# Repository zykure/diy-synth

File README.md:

# diy-synth

Schematics and related files for DIY modular synthesizer components.

## MS-20 VCF

[A voltage controller filter based on the Korg MS-20 design.](./VCF_MS-20)

## AS3340 VCO

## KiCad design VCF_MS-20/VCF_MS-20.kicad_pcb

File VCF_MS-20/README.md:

# diy-synth

Schematics and related files for DIY modular synthesizer components.

## MS-20 VCF

A voltage controlled filter based on the "late" Korg MS-20 design. Original design schematics from [Rene Schmitz](https://www.schmitzbits.de/ms20.html) and [Eddy Bergman](https://www.eddybergman.com/2019/12/synthesizer-build-part-12-korg-ms20.html?m=1).

**Working Falstad circuit simulation (online):** [click here][1]

### Features

* Designed for Eurorack format with a 6 HP frontplate and standard +/- 12 V power supply.
* Frontplate potentiometers to control filter cutoff, resonance, input level, and cutoff CV amount.
* Input jacks for source audio signal and cutoff CV; output jack for filtered audio signal.
* Quad opamp (LM324N) and dual OTA (LM13700) in the main circuit.
* LEDs in the resonance feedback circuit indicate resonance "drive".

### Layout

* Circuit schematics: [VCF_MS-20_plan.pdf](./schematics/VCF_MS-20_plan.pdf)
* Board layout: [VCF_MS-20_pcb.pdf](./schematics/VCF_MS-20_pcb.pdf) ([*mirrored*](./schematics/VCF_MS-20_pcb_mir.pdf))
   * The board is a 21 x 36 hole (56 x 97 mm) perforated PCB that should fit in most Eurorack cases. The required depth is about 60 mm.
* Board layout with frontplate design: [VCF_MS-20_pcb_all.pdf](./schematics/VCF_MS-20_pcb_all.pdf)
   * The frontplate is designed for Eurorack cases and has a size of 3 U x 6 HP (127 x 30.5 mm)

### Components (BOM)

*Estimated costs ~ 25 Euro* (in Germany, as of Nov 2023)

|Item |Qty  |Reference(s)                  |Value          |Datasheet                                         |Note           |
|----:|----:|-----------------------------:|--------------:|--------------------------------------------------|---------------|
|    1|    1|                            C1|           4.7n|~                                                 |               |
|    2|    2|                        C2, C3|           1.0n|~                                                 |film cap.      |
|    3|    2|                        C4, C5|           100n|~                                                 |               |
|    4|    1|                            C6|           1.0u|~                                                 |optional       |
|    5|    1|                            C8|           470n|~                                                 |film cap.      |
|    6|    2|                        D1, D2|            LED|~                                                 |               |
|    7|    1|                            J1|          POWER|~                                                 |               |
|    8|    1|                            J2|       AUDIO IN|~                                                 |               |
|    9|    1|                            J3|      AUDIO OUT|~                                                 |               |
|   10|    1|                            J4|          CV IN|~                                                 |               |
|   11|    2|                        Q1, Q2|         BC558C|https://www.onsemi.com/pub/Collateral/BC556BTA-D.pdf|matched      |
|   12|    1|                            R1|           200k|~                                                 |optional       |
|   13|    2|                        R2, R3|           100k|~                                                 |               |
|   14|    6|       R4, R5, R6, R7, R9, R10|            10k|~                                                 |               |
|   15|    1|                            R8|           8.2k|~                                                 |or trimpot     |
|   16|    1|                           R11|           4.7k|~                                                 |               |
|   17|    1|                           R12|           470k|~                                                 |               |
|   18|    1|                           R13|           2.2k|~                                                 |               |
|   19|    1|                           R14|           1.5k|~                                                 |               |
|   20|    4|            R15, R16, R17, R18|            220|~                                                 |               |
|   21|    2|                      RV1, RV4|    100k / log.|~                                                 |Resonance/Input level ctrl.|
|   22|    2|                      RV2, RV3|    100k / lin.|~                                                 |Cutoff/CV amount ctrl.|
|   23|    1|                           SW1|     SW_DPDT_x2|~                                                 |HP/LP mode     |
|   24|    1|                           SW2|        SW_SPDT|~                                                 |6/12 dB falloff|
|   25|    1|                            U1|          LM324|http://www.ti.com/lit/ds/symlink/lm2902-n.pdf     |               |
|   26|    1|                            U2|        LM13700|http://www.ti.com/lit/ds/symlink/lm13700.pdf      |               |

Notes:
* Use film capacitors in the audio signal path, not ceramic ones. (Ceramic ones have a voltage dependency that causes distortions.)
* The feedback resistor R8 may be tuned to change the resonance characteristics, e.g. a trimpot could be used instead of a fixed resistor. Check out the [circuit simulation][1] to see what this does.
* For best results, the two transistors should be matched by their hFE value as good as possible. This can usually be done with a simple multimeter with transistor tester.
* A passive low-pass filter (R1/C6) is added at the audio input to remove any DC voltage offset. This is completely optional and the components could be removed from the circuit.

[1]: https://falstad.com/circuit/circuitjs.html?ctz=CQAgbArCAMB00OgRgCwE4Oa9kAme0AHBBAMxhq6lKEDsYt4uISzGMBiSAUCtMyiRg8fEBFYjoLGAB0AztHl95AWlbzFCjbCibNyueq3G4u+UlVI49amFK1SpCLRpG4KUkRpokaMNAg0IipzBHkAEwBTADMAQwBXABsAF1lDVXdPQm9ff0Dg0m0PALAUXH8qXGgnFFDNKLik1M0LE1hiiFLy-lIqmrqImISUtNa1JHg0QQh0NFJCXFxOiCLcFzpqANol3pQVwzC5BuHm80sJ3BRaaG3CDbBSpEKFWHswXFY7h4+iHwGjoZNNJqVbrbp0Si+ba0DLtcqUbIOPi4KZ-A71QEjTQg4wqdzw3CI0jI1GtKwYxpYyzyRawFFIWh0D7XB7IMCwspg-wQj5oaH-Y5A7GtOBvH4oQh8hYQQgoSCw+yBToLQlVJDOZ7kwaU05yHHY0W0JVgFULZAagWY3U4wiwWUea78YhlB5jQ3vKwSqVLWXy9Hak6jDSrChUa60dA3NAQXCWnVBvX4lyMlG7QjQFCCEOUew3SO0aOx-0A+MtSykHTocjQSDZdVGwighkLOaXdOZsmHQVU9K4uDVMoS3zUQQ3ba1Yvd3Ui7Rs7bvLJWchgdVxk7cWLgFCSFgSS5SQgsZhqZjkxBSftOWwFwJOD6eZiXsgM1A+aoMqiHs8IDcgOXb8YBCEEBAJANAjxAiRvwQED+3PGVxGoZkyiQGgZl0Fhz2gbgAHcjy-Sg-wIx9cPwndUOYfcYFIiUWEI2jFm3bC8IYy4tzwNjmLEQjGLEegOKY0jnGEXjhLoki8LE3xmEgYRpOovDZJ3UopCorjxEo0QxLUoT+Ko7TOgUviRMMwJKMMriGNEBiLJow8lmEUo8FsvDeikQRhFojyjJszzD08QTJL00z+IC6iAGMiJAMLaMcYQpCQSIVHAlR8BNXlCDvGsqEIuCeEisSwsK8gYBYJLwPwPhiXeWtnUCBwOAQHgWP8kqvOA7CACcWEzcieNEBLzxomCqkPbzRqM+ZtyEdzgJmoylPkxb-AWwz5v-FgVq6v85pWjb5sGxBuG60D5pUJyDswo68NOla1F6g7SPO6aVs+TaL1It6GTkwlxOo7qprwO5otlaKStUqpjrBkTgbi6HSsWLjAcJfzQbWCT4fRzHge2+7txRyDerhiHcfkgm1EI4mONxhyd1Sogd0On8TvIfyYxA1m-xg1SsO4SKVD4KQwoF3poozUq4K4DhMwwbKHnEdsXEa5Ans5u8OZNMXBO67yPAEJy9YRqpLJgw3ddF7ChGYOGNK5qRbeYKcVESSJwmkC9Gp4K27bEImSpmfGQCdl23aQCXPdIm2JDcsQJCR-2iaqX3AuipOA9T+24+G9zRcBw2Tft3rBdjkiAba9MQe3CUPbNJHQern2G-jvyhaTpvuAZbc7hz5hu+izWw+gjgFgYLCx7DgAlSI5AAewAO1iOfwsiJ7DeFhuwuw1JUAAivvpAiupDUWD4HEOYHHQp4Fkyw88R0BAKDIfgM3QI0w4gGCp24VJyYr2mVEPpBXcsBWCoGyBQBwDYygn0zHQGM0A-AfElNsKAH8pBfxuqLQBh8aJ+DwAzdAwgcEsTwRXDaOCdbATIU5QB34oYHncoeWhQ08L-ycv-Dqn1+LJTktwiiRl96gQ4VnVhhkhFiLwVxYR1sSqgW2nDUCgM5F-kdHzH2PD1FOXcrAR0Y8sKJWShwBCTwWQbEcPVZWzV1F4OLnI7OIEDYwQFoeAuIFaKCNolxDxX5uFaJok5DRDcNGWQroE0Jni7JHy8k4iJ3VBGi33h1FRLCWDcPcdwi2n1eoAIShIHJRk1AiWsvZAapElJUWuPjUpN1i7CzVuLEJIA-6GWITtIhqkWkfWRJBPcohCnkTSPoYURY9DaDMMYAwbhgwvHGWMKwOi3iEEgFMRkxByhFEXJKKEVwaylE1F2K0CY77FGyFsvkOyHgeA2SUMogQMBUBUvsikgYyxtA6F0O5OZHlriFGcPUqEQF+FYMUQkQgVwwheHwIQko1jvD4IQiFWoSwvL+eMEBJIyAFlbOmZ4+J+AYGfGfdU6zJyHOFEUNkayoyMmjMgZ4xzkAeFQFNJwfI-A-J7PqDkjKRwsvquy0lpZqRyFpKQc+DgUTlCeP+bl0L4EFhpR-J4HLrQijhPi9AgsEFzFQByY2VUIzIHNHYRFByhX-Omcc-V1RDVWHVCalVwIyQTGBcSI0rN6ARj1RqqYiAMAjkda8vQ7RGVrDuPaGsGZ2SCpRb2Bl0LmQ7HJCMkNqAw13EzJGuUgbUUAsqFUa4dwnj2v2O4SlibnwICLEiqcCZg0IHTMgFE58+AXz9DWslfyDTwCsNyaM+Q9gLEcBODtOpVaUQZioLBH1XKg1ArY-hllgLzqcYu-xAE3pBLettfhU7TxQXiiwNBn08kJLyRQtxt9AH5KZj+TukFfqgRPLfdxV1EAcF6DQPRWFSAgAAMLxGSDPaI0Qnq7vCVemdpV8ngY+gAcw1mNJxnNvLwcgpTWR8l1ZobxvDXD2HqIIbhsRkqBHsJEdBsRyj7M0MxlasIW2VNyN-gNqLBu+dCNESPpuvBz6JbcAQ-wua0dHzUQng+l9t83r9I9qIOOEsdDcHE3xp90md7hz6fJi8inlN0bw50IW4M-xi0GuHUwHdrggQdtsKzK0sZh0RtFeBmEWDcAAMqXqFuLFQjGGmlTiIkOQkQEZPWs8eB2ONQu-QUYx8GoXo6yMY0nbCnNnFeYAhvAepUACSc9uCczelRQrNmw4JTkMkeQAB5QD+XNblNEOUkrCM57hCqzVgr57cnHi+qVAAQgAS1iHIfLlmOEmWEAk-jm487ATht5cCeSoJjxYHSK4TxOh8hNAWdUK3LguHeEyWUkqGBvp-K5Nus22qcIQ33Q2t3PFidSXJXhfkNPcdE9piAAmgaQa1gfD22FKtNL-gzPwPMvwCN+kV3qOkbr8ImhTCdLiwP9W4zxSLcOYfA1w1jLiOObNCJs3j9TWMcfVPQ5pI+E1YeEyqdxh6W1Pq-XkoV8nxcJpwwmlIwyVFOfk754ZkSRPI4lV56Lhmdd8Y2fGsLxSPOGtrVypHUG81kay+chN8y7TqKbjMspUQVEvzddPMtyqA55hwrlJlGMUAzfVXKDKOqfJf3QVVprOp4tN61bGmNYCXlX1SAAGKRFdgAI1iOFAA1rwaopUG78PTglDwAB9QgyfoDJ48DMZPVgc-4DT2oZPuAc8p9IDH39Md+lr1E6hWgqf0+Z6vDnjPksEH0E6EsZPhfi+1+T2Xj4Yc+5UU24zaQM0YJWKHwzIf5OZ8HgrpzLiSyq4wT18XFLms1+r-ogHkAU9Z4LyXivSS9EYJ525uXsQv0G4qWTqVdUGe08Z6zygZPEB08gK70gIvOeP59+97Tu9IAT1mVhVnILlgAYDKrirszs1q1uAXlnhJlEjsDuDj5KbGxqbK0sXOxqviIhnFxgQahpHG3AvmnFnFVEwNuGFA4BNprLku-k-o3tnrnqwHaF-j-qhO-mXpQalMDLxokltEeqQPXs-jUB-vap3nAAXt-j3mQP-rwXpt5ALFgR7KhCIUwS-s3hIRwT3k8AobHngmFLxIvruK-poeIbnnAN-t3jnqgAYb+rxEYezJdOqOYQ3lodYR3u-tYbob-q-jwbHpKD9F+PwNNLlEeBoR4ZYS3p-oXvlCAIyPjNPqLFzn+Dot+mPBAElIwNIVMJlFbs7iavYJYqRLQfgoeEkRUUZJUk9okeLPJFxLURUuLLxE0Q0XpMDPvF4szvxF9IzgAB6JE7ZoSJEPTAzTTbjRrhC9akQEyJK9HxRzHy4JSo7UQeblETTNES7+axCBbBaqTcBDEuD4zzCJHiAiBhyTFHgRCzGSTRaaypQ2aL7uZiArTqx6YEZhwBZBYhZBQTb+yhQ0a6QTbswGZOYkQeZTqe7eZYyby7H7F-EgRwlJxPHWz0FPRYzkxYnk5ol0y0w6RDHQkV4lF8FQDEjuQ9QgAAASAACkcRzCNJlMicyYSJ5FSQADL0lDFkAAn2xkBgy-rXFckMkzBCzZBiAyiVzGaoA0n0lw48STpkylKUH7zglhTchx6MHRHyH4A+EECSHv62F7AOF1GEJ-aJ5-juFiG6k6Af4IBIRGmyGZ4BGX77xrzixNyxyiHMEiF6n2lNTRiOl+HiD-4zy7gu6Horh7DTTaZSyqQRnRTcDhnqFNKlQsivQVhWBE6cCDx4CJll4plUCbT370BppiAGnNqfqKjoAuK5n5k8BFm-ouL1GshiAcBhwu75aHgXGB6lb37nhALB5h4R6R7yD779blaLzLzdmYSMB9nRQIxoJAJuYzzxCdTLzyCB6dSRAACO8QkQS8AAnrOWCiAAuQlJwJkVwDkRWdeeeAYowMfNVskAAA6AbyB-qxCvkR79bJDTkrxAA

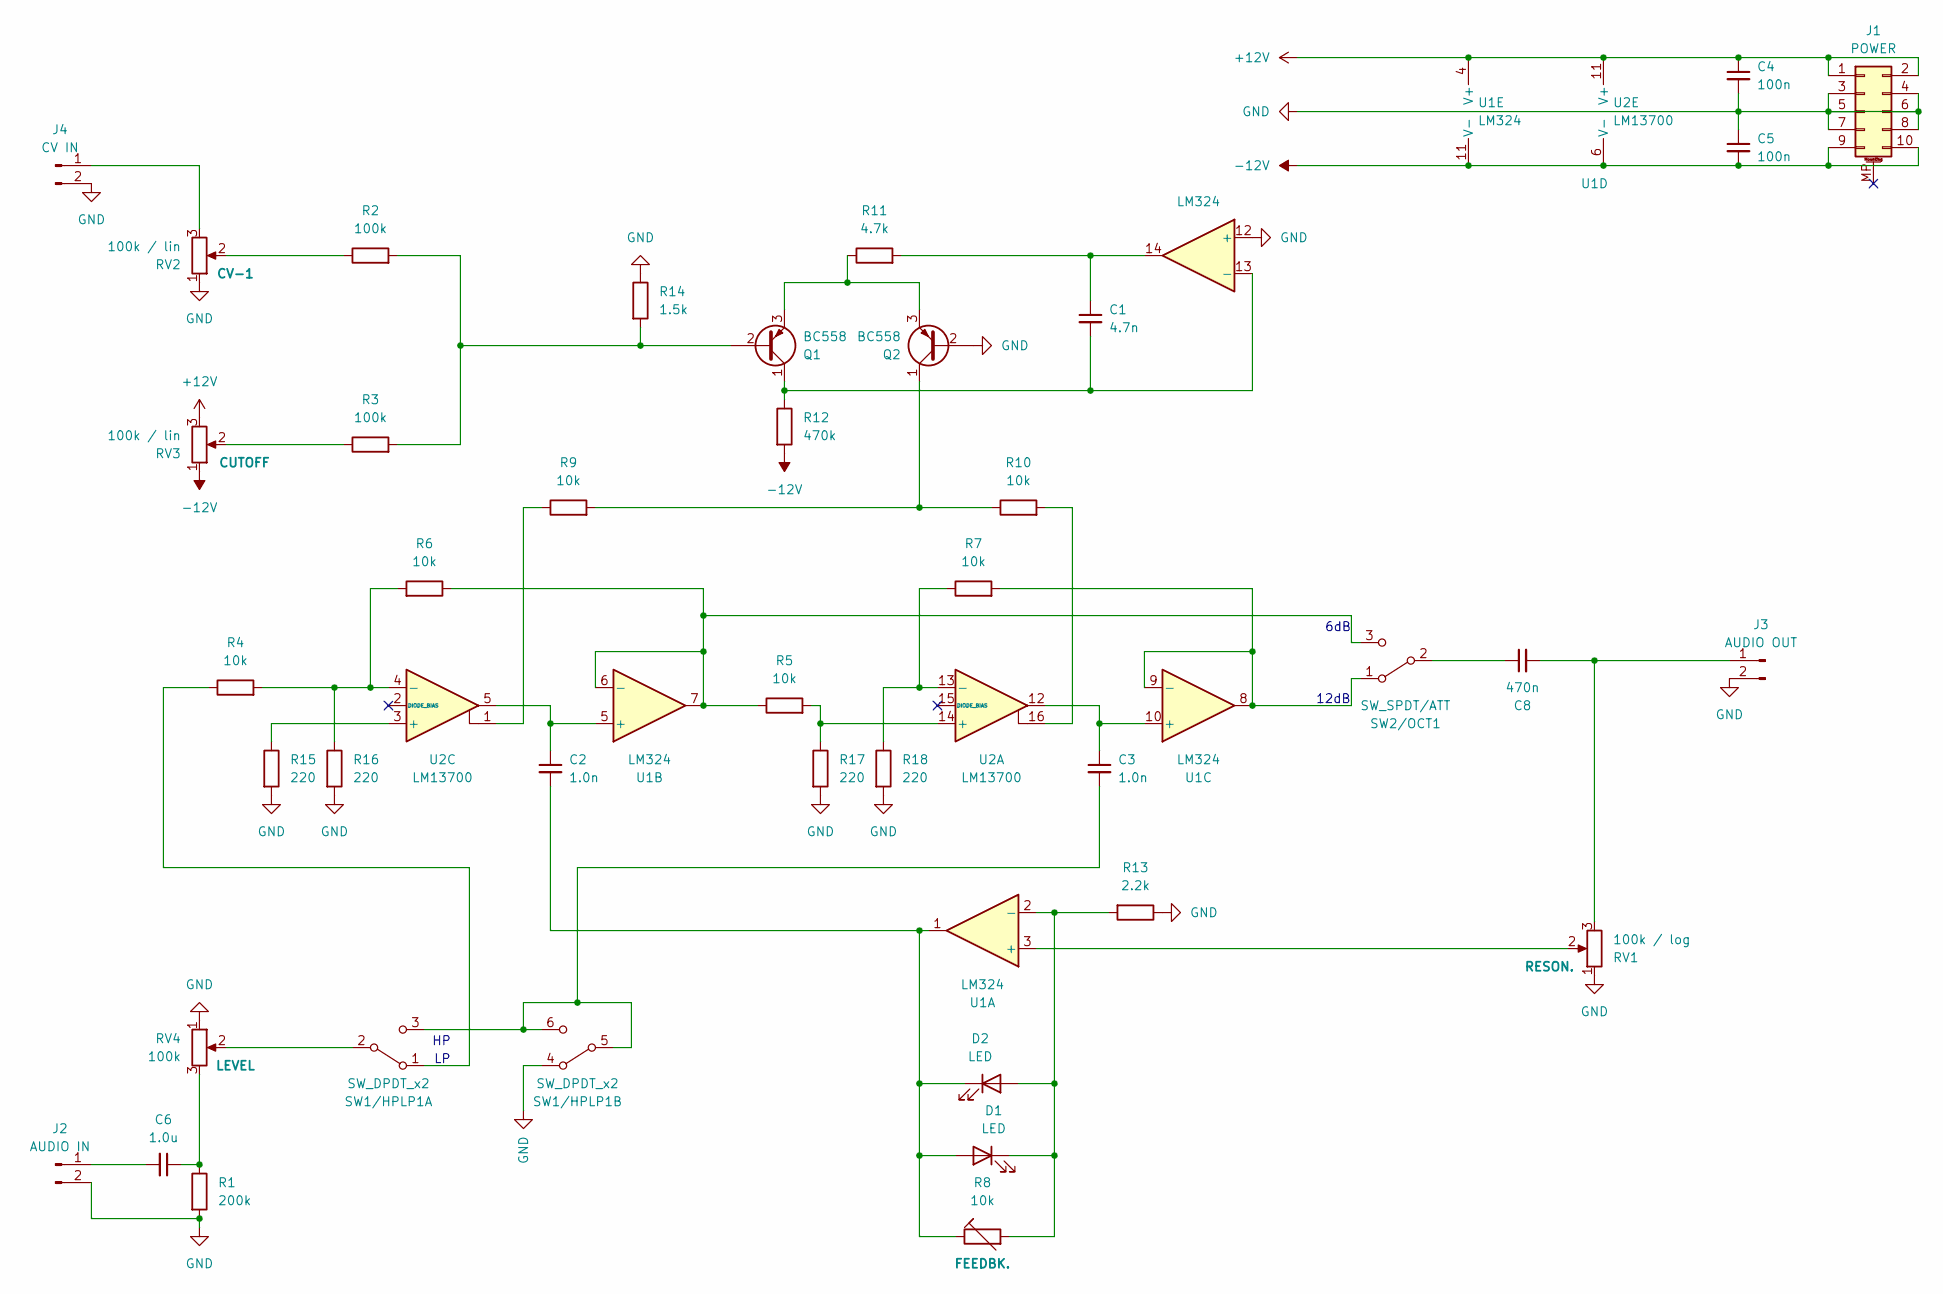
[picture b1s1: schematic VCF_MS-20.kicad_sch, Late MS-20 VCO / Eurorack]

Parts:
C1: 4.7n; C_Disc_D7.5mm_W2.5mm_P5.00mm
C2, C3: 1.0n; C_Disc_D7.5mm_W2.5mm_P5.00mm
C4, C5: 100n; C_Disc_D7.5mm_W2.5mm_P5.00mm
C6: 1.0u; C_Disc_D7.5mm_W2.5mm_P5.00mm
C8: 470n; C_Disc_D7.5mm_W2.5mm_P5.00mm
D1, D2: LED; LED_D3.0mm
J1: POWER; PinHeader_2x05_P2.54mm_Vertical
J2: AUDIO IN; PinHeader_2x01_P2.54mm_Vertical
J3: AUDIO OUT; PinHeader_2x01_P2.54mm_Vertical
J4: CV IN; PinHeader_2x01_P2.54mm_Vertical
Q1, Q2: BC558; TO-92_Inline_Wide
R1: 200k; R_Axial_DIN0207_L6.3mm_D2.5mm_P15.24mm_Horizontal
R2, R3: 100k; R_Axial_DIN0207_L6.3mm_D2.5mm_P15.24mm_Horizontal
R4, R5, R6, R7, R9, R10: 10k; R_Axial_DIN0207_L6.3mm_D2.5mm_P15.24mm_Horizontal
R8: 10k
R11: 4.7k; R_Axial_DIN0207_L6.3mm_D2.5mm_P15.24mm_Horizontal
R12: 470k; R_Axial_DIN0207_L6.3mm_D2.5mm_P15.24mm_Horizontal
R13: 2.2k; R_Axial_DIN0207_L6.3mm_D2.5mm_P15.24mm_Horizontal
R14: 1.5k; R_Axial_DIN0207_L6.3mm_D2.5mm_P15.24mm_Horizontal
R15, R16, R17, R18: 220; R_Axial_DIN0207_L6.3mm_D2.5mm_P15.24mm_Horizontal
RV1: 100k / log; Potentiometer_TT_P0915N
RV2, RV3: 100k / lin; Potentiometer_TT_P0915N
RV4: 100k; Potentiometer_TT_P0915N
SW1/HPLP1: SW_DPDT_x2; PinHeader_2x03_P2.00mm_Vertical
SW2/OCT1: SW_SPDT/ATT; PinHeader_1x03_P2.00mm_Vertical
U1: LM324; DIP-14_W7.62mm
U2: LM13700; DIP-16_W7.62mm

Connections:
+12V: C4.1, J1.1, J1.2, RV3.3, U1.4 (V+), U2.11 (V+)
-12V: C5.2, J1.9, J1.10, R12.2, RV3.1, U1.11 (V-), U2.6 (V-)
GND: C4.2, C5.1, J1.3, J1.4, J1.5, J1.6, J1.7, J1.8, J2.2, J3.2, J4.2, Q2.2 (B), R1.2, R13.1, R14.1, R15.2, R16.2, R17.2, R18.2, RV1.1, RV2.1, RV4.1, SW1/HPLP1.4 (A), U1.12 (+)
unnamed: C1.1, R11.2, U1.14
unnamed: C6.1, R1.1, RV4.3
unnamed: C2.2, D1.2 (A), D2.1 (K), R8.1, U1.1
unnamed: D1.1 (K), D2.2 (A), R8.2, R13.2, U1.2 (-)
unnamed: C6.2, J2.1
unnamed: C8.2, J3.1, RV1.3
unnamed: J4.1, RV2.3
unnamed: Q1.2 (B), R2.2, R3.2, R14.2
unnamed: C1.2, Q1.1 (C), R12.1, U1.13 (-)
unnamed: Q1.3 (E), Q2.3 (E), R11.1
unnamed: Q2.1 (C), R9.2, R10.1
unnamed: R2.1, RV2.2
unnamed: R3.1, RV3.2
unnamed: R9.1, U2.1
unnamed: R10.2, U2.16
unnamed: R4.1, SW1/HPLP1.1 (A)
unnamed: RV4.2, SW1/HPLP1.2 (B)
unnamed: C3.2, SW1/HPLP1.3 (C), SW1/HPLP1.5 (B), SW1/HPLP1.6 (C)
unnamed: R7.2, SW2/OCT1.1 (A), U1.8, U1.9 (-)
unnamed: C8.1, SW2/OCT1.2 (B)
unnamed: R5.1, R6.1, SW2/OCT1.3 (C), U1.6 (-), U1.7
unnamed: RV1.2, U1.3 (+)
unnamed: C2.1, U1.5 (+), U2.5
unnamed: C3.1, U1.10 (+), U2.12
unnamed: R5.2, R17.1, U2.14 (+)
unnamed: R7.1, R18.1, U2.13 (-)
unnamed: R15.1, U2.3 (+)
unnamed: R4.2, R6.2, R16.1, U2.4 (-)

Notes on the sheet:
6dB
12dB

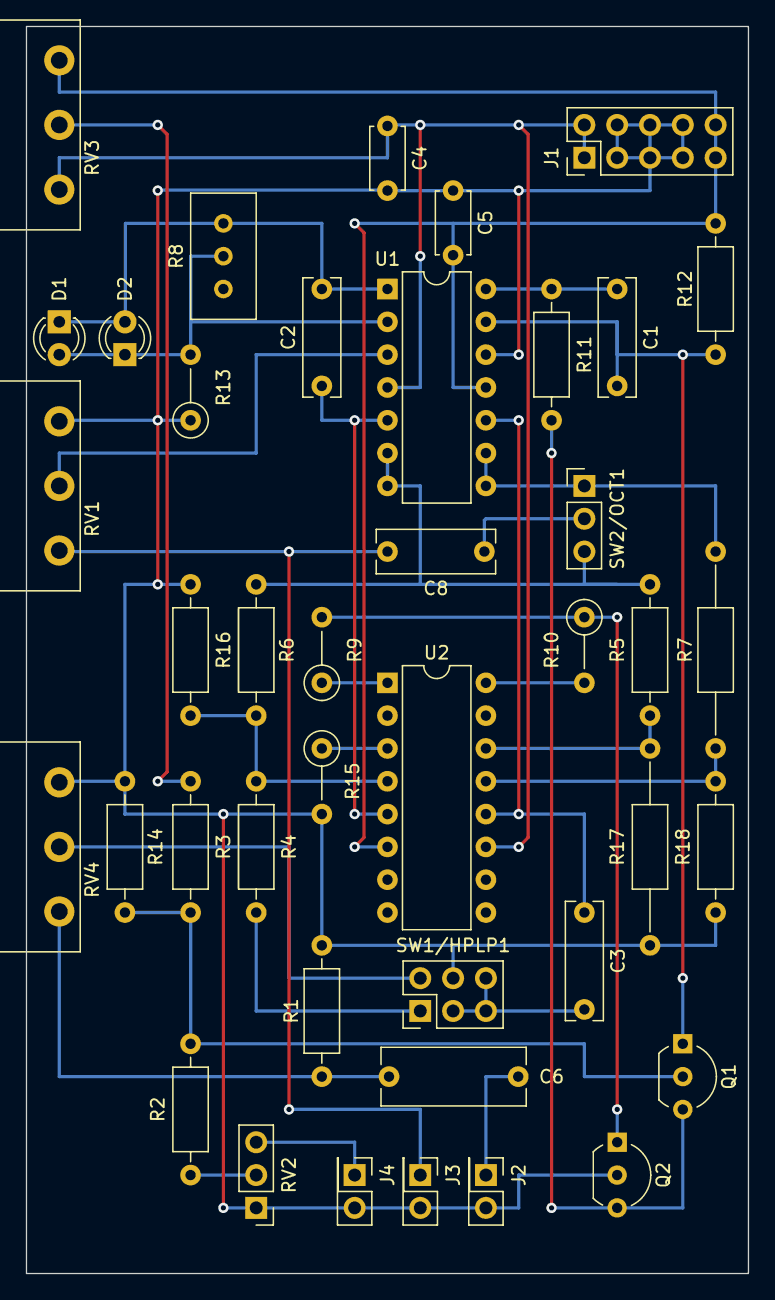
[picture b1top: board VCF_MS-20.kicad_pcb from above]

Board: 2 copper layers, 55.9 x 96.5 mm, 41 parts (0 on the bottom side), 31 nets.

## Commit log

2023-11-09 [VCF] Add KiCad files
2023-11-09 Update MS-20 VCO
2023-11-09 Move README files
2023-11-09 Update pcb
2023-11-14 Fix PDFs
2023-11-20 Update pcb, change R8, add mirror view
2023-11-20 Update pics
2023-12-18 Update / fix PDFs
